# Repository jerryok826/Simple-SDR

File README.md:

# Simple-SDR
Simple-SDR is a basic Software Defined Receiver for experimentation

## Project Description
The SDR board has the basic components of a 20 meter Ham band SDR receiver. The sections are:
1. A 1.5MHz HPF to reject Broadcast band signals.
2. A 20 meter Ham band BPF.
3. RF Preamp.
4. A Tayloe quadrature detector
5. I and Q clock generator.
6. SI5351 programmable clock
7. I&Q Audio amps

Other SDR projects of interest:

https://community.element14.com/challenges-projects/project14/radiocontrol/b/blog/posts/software-defined-radio-sdr-experiment-board

https://github.com/ukagit/sdr_kiss

https://github.com/do7jbh/SSR-2

https://github.com/DD4WH/Teensy-ConvolutionSDR.

https://github.com/Dizzerin/Software-Defined-Radio

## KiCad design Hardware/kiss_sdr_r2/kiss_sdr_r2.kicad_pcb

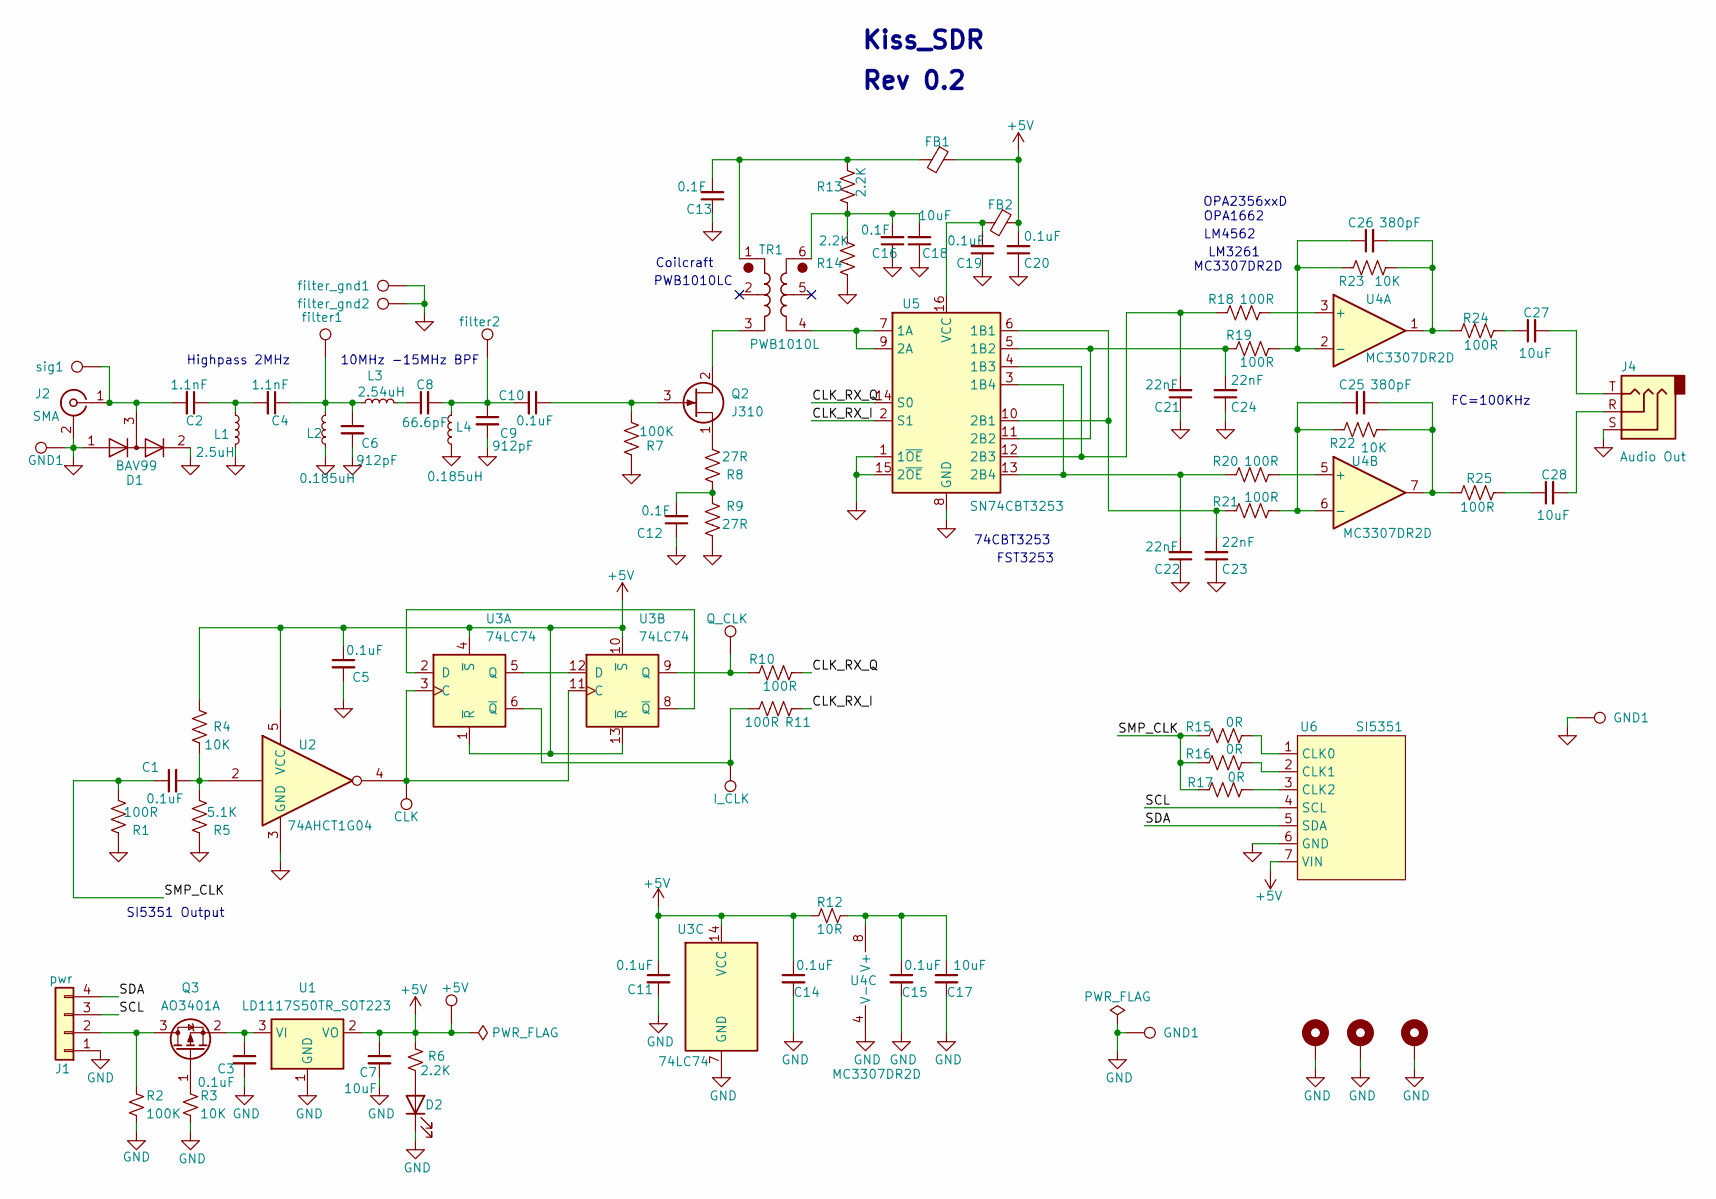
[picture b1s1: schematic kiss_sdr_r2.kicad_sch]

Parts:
+5V1: +5V; TestPoint_THTPad_D2.0mm_Drill1.0mm
C1, C3, C5, C10, C11, C14, C15, C19, C20: 0.1uF; C_0805_2012Metric_Pad1.18x1.45mm_HandSolder
C2, C4: 1.1nF; C_0805_2012Metric_Pad1.18x1.45mm_HandSolder
C6, C9: 912pF; C_0805_2012Metric_Pad1.18x1.45mm_HandSolder
C7, C17, C18, C27, C28: 10uF; C_0805_2012Metric_Pad1.18x1.45mm_HandSolder
C8: 66.6pF; C_0805_2012Metric_Pad1.18x1.45mm_HandSolder
C12, C13, C16: 0.1F; C_0805_2012Metric_Pad1.18x1.45mm_HandSolder
C21, C22, C23, C24: 22nF; C_0805_2012Metric_Pad1.18x1.45mm_HandSolder
C25, C26: 380pF; C_0805_2012Metric_Pad1.18x1.45mm_HandSolder
CLK1: CLK; TestPoint_THTPad_D2.0mm_Drill1.0mm
D1: BAV99; SOT-23
D2: OC_Fault; LED_1206_3216Metric_Pad1.42x1.75mm_HandSolder
FB1, FB2: FerriteBead, 6A 1 9mΩ 33Ω@100MHz ±25% 1206 Ferrit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; L_1206_3216Metric_Pad1.42x1.75mm_HandSolder
GND1, GND2, GND3: GND1; TestPoint_THTPad_D2.0mm_Drill1.0mm
H2, H3, H4: MountingHole_Pad; MountingHole_2.7mm_M2.5_ISO14580_Pad
I_CLK1: I_CLK; TestPoint_THTPad_D2.0mm_Drill1.0mm
J1: pwr; PinHeader_1x04_P2.54mm_Vertical
J2: SMA; SMA_Samtec_SMA-J-P-X-ST-EM1_EdgeMount
J4: Audio Out; Jack_3.5mm_CUI_SJ-3523-SMT_Horizontal
L1: 2.5uH; L_1206_3216Metric_Pad1.22x1.90mm_HandSolder
L2, L4: 0.185uH; L_1206_3216Metric_Pad1.22x1.90mm_HandSolder
L3: 2.54uH; L_1206_3216Metric_Pad1.22x1.90mm_HandSolder
Q2: J310; SOT-23
Q3: AO3401A; SOT-23
Q_CLK1: Q_CLK; TestPoint_THTPad_D2.0mm_Drill1.0mm
R1, R10, R11, R18, R19, R20, R21, R24, R25: 100R; R_0805_2012Metric_Pad1.20x1.40mm_HandSolder
R2, R7: 100K; R_0805_2012Metric_Pad1.20x1.40mm_HandSolder
R3, R4, R22, R23: 10K; R_0805_2012Metric_Pad1.20x1.40mm_HandSolder
R5: 5.1K; R_0805_2012Metric_Pad1.20x1.40mm_HandSolder
R6, R13, R14: 2.2K; R_0805_2012Metric_Pad1.20x1.40mm_HandSolder
R8, R9: 27R; R_0805_2012Metric_Pad1.20x1.40mm_HandSolder
R12: 10R; R_0805_2012Metric_Pad1.20x1.40mm_HandSolder
R15, R16, R17: 0R; R_0805_2012Metric_Pad1.20x1.40mm_HandSolder
TR1: PWB1010L; Transformer_Coilcraft_PWB1010
U1: LD1117S50TR_SOT223; SOT-223-3_TabPin2
U2: 74AHCT1G04; SOT-23-5
U3: 74LC74; SO-14_5.3x10.2mm_P1.27mm
U4: MC3307DR2D; SOIC-8_3.9x4.9mm_P1.27mm
U5: SN74CBT3253; SO-16_3.9x9.9mm_P1.27mm
U6: SI5351; SI5351_Brd_fp
sig1: sig1; TestPoint_THTPad_D2.0mm_Drill1.0mm
sig2: filter1; TestPoint_THTPad_D2.0mm_Drill1.0mm
sig3: filter_gnd1; TestPoint_THTPad_D2.0mm_Drill1.0mm
sig4: filter_gnd2; TestPoint_THTPad_D2.0mm_Drill1.0mm
sig5: filter2; TestPoint_THTPad_D2.0mm_Drill1.0mm

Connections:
+5V: +5V1.1, C5.1, C7.1, C11.1, C14.1, C20.2, FB1.1, FB2.1, R4.2, R6.2, R12.2, U1.2 (VO), U2.5 (VCC), U3.1 (~R), U3.4 (~S), U3.10 (~S), U3.13 (~R), U3.14 (VCC), U6.7 (VIN)
/CLK_RX_I: R11.2, U5.2 (S1)
/CLK_RX_Q: R10.2, U5.14 (S0)
/SCL: J1.3, U6.4 (SCL)
/SDA: J1.4, U6.5 (SDA)
/SMP_CLK: C1.1, R1.2, R15.1, R16.1, R17.1
GND: C3.2, C5.2, C6.2, C7.2, C9.2, C11.2, C12.1, C13.1, C14.2, C15.2, C16.1, C17.2, C18.1, C19.1, C20.1, C21.1, C22.1, C23.1, C24.1, D1.1 (K), D1.2 (A), D2.1 (K), GND1.1, GND2.1, GND3.1, H2.1, H3.1, H4.1, J1.1, J2.2 (Ext), J4.S, L1.2, L2.1, L4.1, R1.1, R2.2, R3.2, R5.1, R7.1, R9.1, R14.1, U1.1 (GND), U2.3 (GND), U3.7 (GND), U4.4 (V-), U5.1 (1~OE), U5.8 (GND), U5.15 (2~OE), U6.6 (GND), sig3.1, sig4.1
unnamed: C1.2, R4.1, R5.2, U2.2
unnamed: C2.1, C4.2, L1.1
unnamed: C4.1, C6.1, L2.2, L3.1, sig2.1
unnamed: C8.1, L3.2
unnamed: C8.2, C9.1, C10.2, L4.2, sig5.1
unnamed: C12.2, R8.1, R9.2
unnamed: C13.2, FB1.2, R13.2, TR1.1
unnamed: C16.2, C18.2, R13.1, R14.2, TR1.6
unnamed: C25.2, R22.2, R25.1, U4.7
unnamed: C26.2, R23.2, R24.1, U4.1
unnamed: C27.1, R24.2
unnamed: C27.2, J4.T
unnamed: C28.1, R25.2
unnamed: C28.2, J4.R
unnamed: D2.2 (A), R6.1
unnamed: J1.2, Q3.3 (D), R2.1
unnamed: C2.2, D1.3 (K), J2.1 (In), sig1.1
unnamed: Q2.2 (D), TR1.3
unnamed: C10.1, Q2.3 (G), R7.2
unnamed: Q2.1 (S), R8.2
unnamed: Q3.1 (G), R3.1
unnamed: C3.1, Q3.2 (S), U1.3 (VI)
unnamed: CLK1.1, U2.4, U3.3 (C), U3.11 (C)
unnamed: U3.2 (D), U3.8 (~Q)
unnamed: U3.5 (Q), U3.12 (D)
unnamed: I_CLK1.1, R11.1, U3.6 (~Q)
unnamed: Q_CLK1.1, R10.1, U3.9 (Q)
unnamed: R18.2, U4.3 (+)
unnamed: C26.1, R19.2, R23.1, U4.2 (-)
unnamed: R20.2, U4.5 (+)
unnamed: C25.1, R21.2, R22.1, U4.6 (-)
unnamed: C15.1, C17.1, R12.1, U4.8 (V+)
unnamed: TR1.4, U5.7 (1A), U5.9 (2A)
unnamed: C23.2, R21.1, U5.6 (1B1), U5.10 (2B1)
unnamed: C24.2, R19.1, U5.5 (1B2), U5.11 (2B2)
unnamed: C21.2, R18.1, U5.4 (1B3), U5.12 (2B3)
unnamed: C22.2, R20.1, U5.3 (1B4), U5.13 (2B4)
unnamed: C19.2, FB2.2, U5.16 (VCC)
unnamed: R15.2, U6.1 (CLK0)
unnamed: R16.2, U6.2 (CLK1)
unnamed: R17.2, U6.3 (CLK2)

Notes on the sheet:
10MHz -15MHz BPF
Highpass 2MHz
Coilcraft
Kiss_SDR
OPA2356xxD
FC=100KHz
MC3307DR2D
Rev 0.2
LM3261
OPA1662
SI5351 Output
74CBT3253
FST3253
LM4562
PWB1010LC

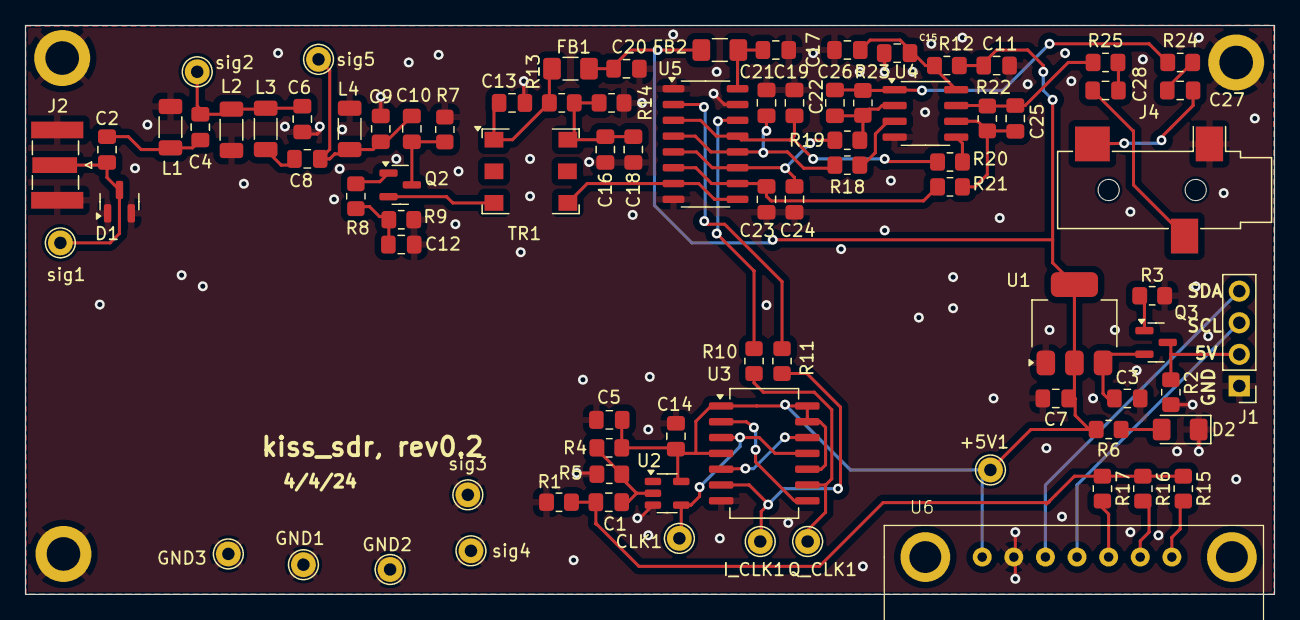
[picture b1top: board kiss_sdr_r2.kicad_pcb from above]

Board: 2 copper layers, 100.4 x 45.7 mm, 88 parts (0 on the bottom side), 48 nets.

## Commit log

2024-04-23 add sdr files
2024-04-23 update photos
2024-04-23 update current files
2024-04-24 update docs
